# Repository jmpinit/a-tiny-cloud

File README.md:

# A Tiny Cloud

**The Goal**: serve a blog from a load-balanced cloud of networked ATtiny10 microcontrollers.

**The Plan:**

1. Make a device that can program and communicate with an array of ATtiny10s via USB
2. Use the TUN/TAP driver in Linux to create a network interface for each ATtiny10. Behind the scenes data is shuffled over USB and then over serial to and from the microcontrollers.
3. Set up NGINX to load-balance requests from the WWW across the microcontrollers.
4. Write a blog engine in AVR assembly.
5. Uh...
6. Profit?

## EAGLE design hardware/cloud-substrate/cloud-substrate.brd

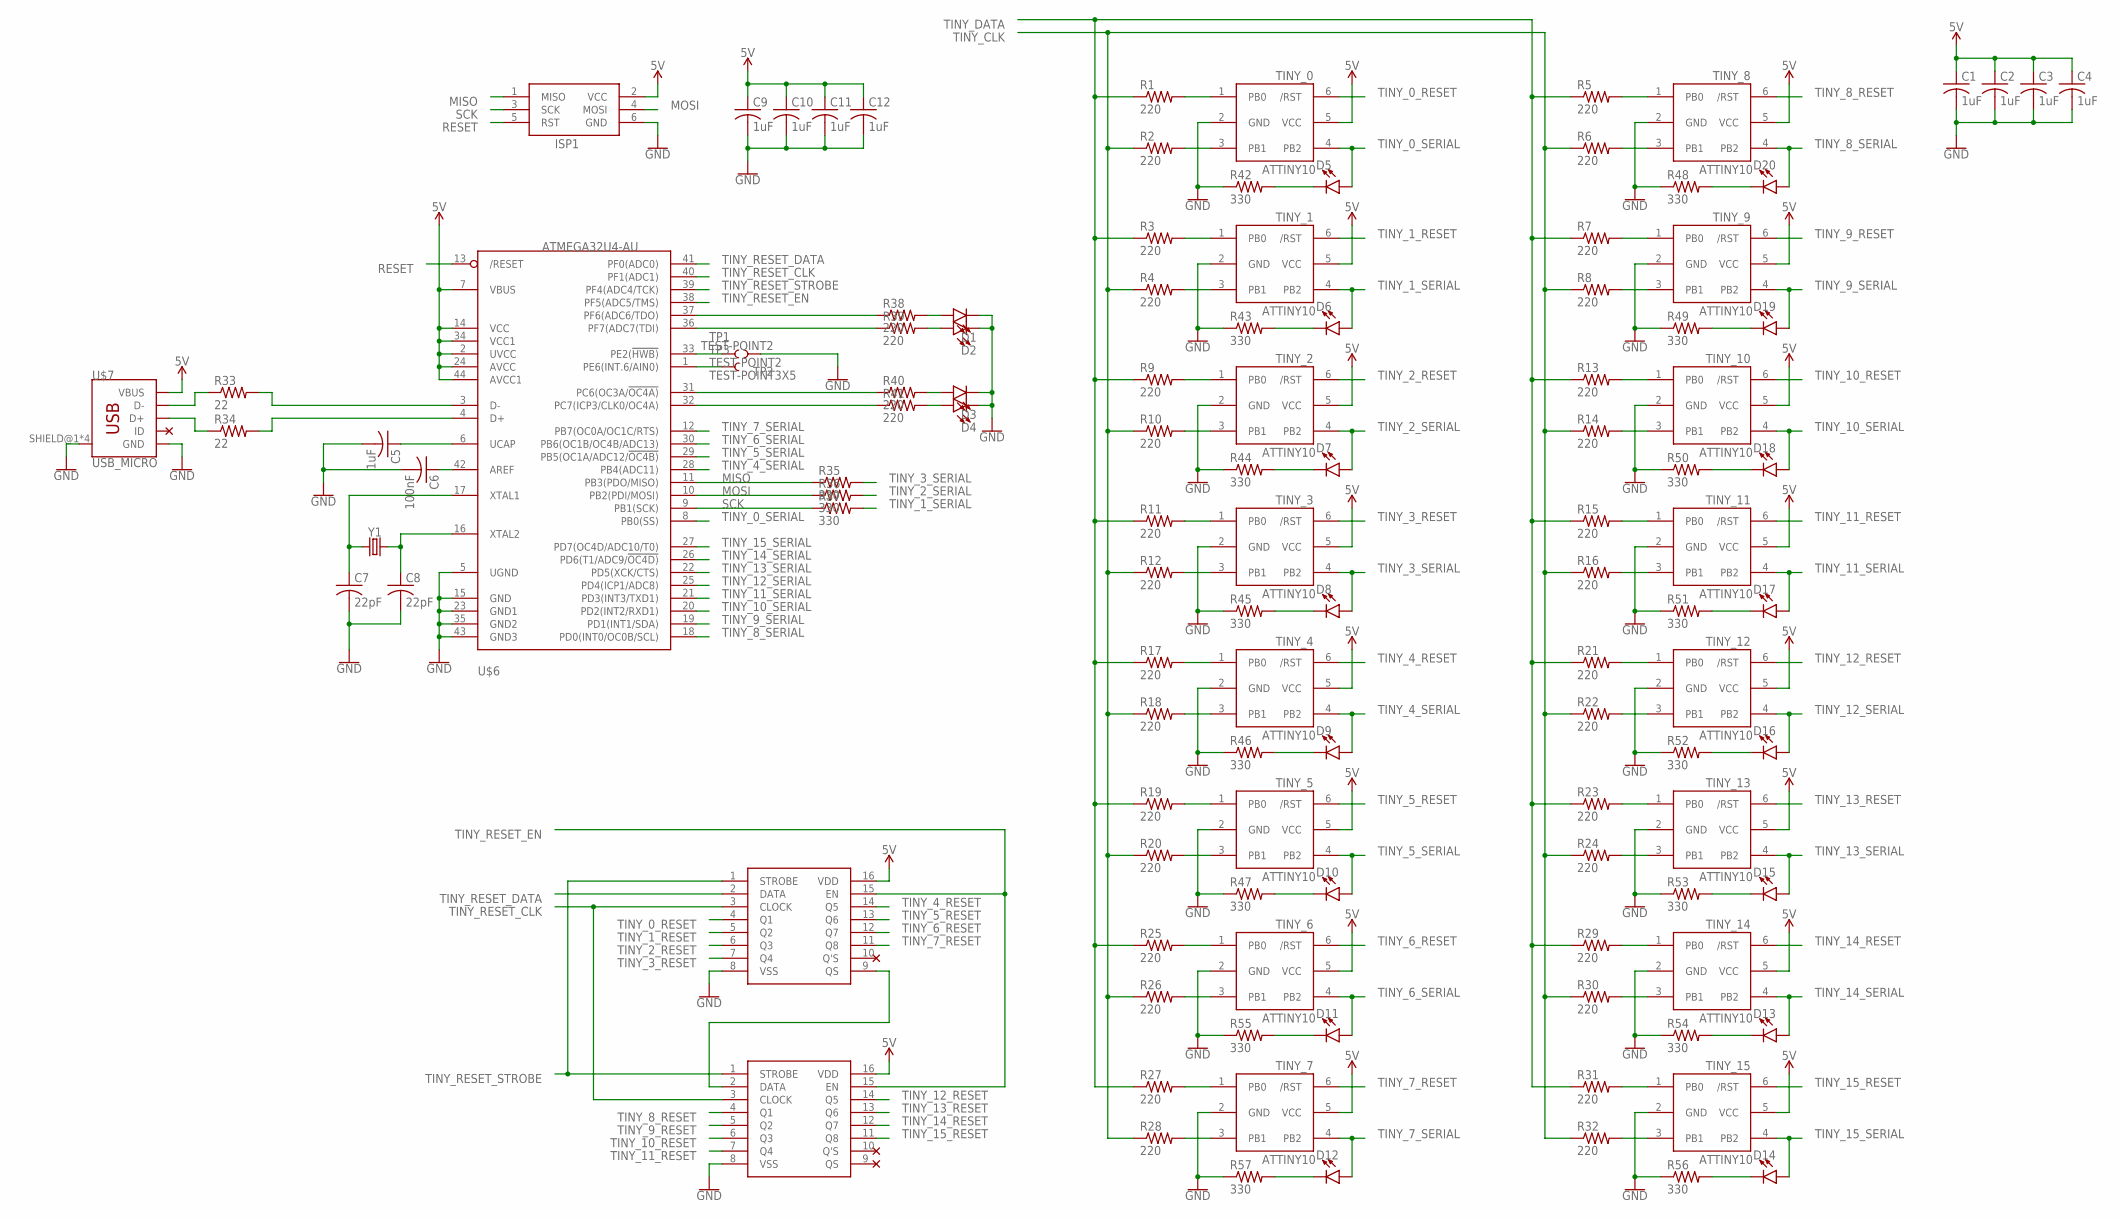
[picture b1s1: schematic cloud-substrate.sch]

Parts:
C1, C2, C3, C4, C9, C10, C11, C12: 1uF; C0805
C5: 1uF; C0402
C6: 100nF; C0402
C7, C8: 22pF; C0402
D1, D2, D3, D4, D5, D6, D7, D8, D9, D10, D11, D12, D13, D14, D15, D16, D17, D18, D19, D20: LED0603; LED-0603
ISP1: AVRISP-6; AVRISP
R1, R2, R3, R4, R5, R6, R7, R8, R9, R10, R11, R12, R13, R14, R15, R16, R17, R18, R19, R20, R21, R22, R23, R24, R25, R26, R27, R28, R29, R30, R31, R32, R38, R39, R40, R41: 220; R0402
R33, R34: 22; R0402
R35, R36, R37, R42, R43, R44, R45, R46, R47, R48, R49, R50, R51, R52, R53, R54, R55, R56, R57: 330; R0402
TINY_0, TINY_1, TINY_2, TINY_3, TINY_4, TINY_5, TINY_6, TINY_7, TINY_8, TINY_9, TINY_10, TINY_11, TINY_12, TINY_13, TINY_14, TINY_15: ATTINY10; SOT23-6
TP1, TP2: TEST-POINT2; PAD.02X.02
TP3: TEST-POINT3X5; PAD.03X.05
U$1, U$2: CD4094B; TSSOP16
U$6: ATMEGA32U4-AU; TQFP44
U$7: USB_MICRO; USB_FCI_10118194
Y1: CRYSTALSMD-3.2X2.5; CRYSTAL-SMD-3.2X2.5MM

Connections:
5V: C1.1, C2.1, C3.1, C4.1, C9.1, C10.1, C11.1, C12.1, ISP1.2 (VCC), TINY_0.5 (VCC), TINY_1.5 (VCC), TINY_2.5 (VCC), TINY_3.5 (VCC), TINY_4.5 (VCC), TINY_5.5 (VCC), TINY_6.5 (VCC), TINY_7.5 (VCC), TINY_8.5 (VCC), TINY_9.5 (VCC), TINY_10.5 (VCC), TINY_11.5 (VCC), TINY_12.5 (VCC), TINY_13.5 (VCC), TINY_14.5 (VCC), TINY_15.5 (VCC), U$1.16 (VDD), U$2.16 (VDD), U$6.2 (UVCC), U$6.7 (VBUS), U$6.14 (VCC), U$6.24 (AVCC), U$6.34 (VCC1), U$6.44 (AVCC1), U$7.1 (VBUS)
GND: C1.2, C2.2, C3.2, C4.2, C5.2, C6.2, C7.2, C8.2, C9.2, C10.2, C11.2, C12.2, D1.C, D2.C, D3.C, D4.C, ISP1.6 (GND), R42.1, R43.1, R44.1, R45.1, R46.1, R47.1, R48.1, R49.1, R50.1, R51.1, R52.1, R53.1, R54.1, R55.1, R56.1, R57.1, TINY_0.2 (GND), TINY_1.2 (GND), TINY_2.2 (GND), TINY_3.2 (GND), TINY_4.2 (GND), TINY_5.2 (GND), TINY_6.2 (GND), TINY_7.2 (GND), TINY_8.2 (GND), TINY_9.2 (GND), TINY_10.2 (GND), TINY_11.2 (GND), TINY_12.2 (GND), TINY_13.2 (GND), TINY_14.2 (GND), TINY_15.2 (GND), TP2.P$1, U$1.8 (VSS), U$2.8 (VSS), U$6.5 (UGND), U$6.15 (GND), U$6.23 (GND1), U$6.35 (GND2), U$6.43 (GND3), U$7.5 (GND), U$7.SHIELD@1 (SHIELD), U$7.SHIELD@2 (SHIELD), U$7.SHIELD@3 (SHIELD), U$7.SHIELD@4 (SHIELD)
MISO: ISP1.1 (MISO), R35.1, U$6.11 (PB3(PDO/MISO))
MOSI: ISP1.4 (MOSI), R36.1, U$6.10 (PB2(PDI/MOSI))
unnamed: R3.2, TINY_1.1 (PB0)
unnamed: R4.2, TINY_1.3 (PB1)
unnamed: R1.2, TINY_0.1 (PB0)
unnamed: R2.2, TINY_0.3 (PB1)
unnamed: R33.1, U$7.2 (D-)
unnamed: R34.1, U$7.3 (D+)
unnamed: R33.2, U$6.3 (D-)
unnamed: R34.2, U$6.4 (D+)
unnamed: U$1.9 (QS), U$2.2 (DATA)
unnamed: R5.2, TINY_8.1 (PB0)
unnamed: R6.2, TINY_8.3 (PB1)
unnamed: C5.1, U$6.6 (UCAP)
unnamed: C6.1, U$6.42 (AREF)
unnamed: R7.2, TINY_9.1 (PB0)
unnamed: R8.2, TINY_9.3 (PB1)
unnamed: C7.1, U$6.17 (XTAL1), Y1.1
unnamed: C8.1, U$6.16 (XTAL2), Y1.3 (2)
unnamed: R9.2, TINY_2.1 (PB0)
unnamed: R10.2, TINY_2.3 (PB1)
unnamed: TP1.P$1, U$6.33 (PE2(!HWB))
unnamed: R38.1, U$6.37 (PF6(ADC6/TDO))
unnamed: R11.2, TINY_3.1 (PB0)
unnamed: R12.2, TINY_3.3 (PB1)
unnamed: R39.1, U$6.36 (PF7(ADC7(TDI))
unnamed: R40.1, U$6.31 (PC6(OC3A/!OC4A))
unnamed: R13.2, TINY_10.1 (PB0)
unnamed: R14.2, TINY_10.3 (PB1)
unnamed: R41.1, U$6.32 (PC7(ICP3/CLK0/OC4A))
unnamed: D1.A, R38.2
unnamed: R15.2, TINY_11.1 (PB0)
unnamed: R16.2, TINY_11.3 (PB1)
unnamed: D2.A, R39.2
unnamed: D3.A, R40.2
unnamed: R17.2, TINY_4.1 (PB0)
unnamed: R18.2, TINY_4.3 (PB1)
unnamed: D4.A, R41.2
unnamed: D7.C, R44.2
unnamed: R19.2, TINY_5.1 (PB0)
unnamed: R20.2, TINY_5.3 (PB1)
unnamed: TP3.P$1, U$6.1 (PE6(INT.6/AIN0))
unnamed: D8.C, R45.2
unnamed: R21.2, TINY_12.1 (PB0)
unnamed: R22.2, TINY_12.3 (PB1)
unnamed: D9.C, R46.2
unnamed: D10.C, R47.2
unnamed: R23.2, TINY_13.1 (PB0)
unnamed: R24.2, TINY_13.3 (PB1)
unnamed: D11.C, R55.2
unnamed: D12.C, R57.2
unnamed: R25.2, TINY_6.1 (PB0)
unnamed: R26.2, TINY_6.3 (PB1)
unnamed: D14.C, R56.2
unnamed: D13.C, R54.2
unnamed: R27.2, TINY_7.1 (PB0)
unnamed: R28.2, TINY_7.3 (PB1)
unnamed: D15.C, R53.2
unnamed: D16.C, R52.2
unnamed: R29.2, TINY_14.1 (PB0)
unnamed: R30.2, TINY_14.3 (PB1)
unnamed: D17.C, R51.2
unnamed: D18.C, R50.2
unnamed: R31.2, TINY_15.1 (PB0)
unnamed: R32.2, TINY_15.3 (PB1)
unnamed: D20.C, R48.2
unnamed: D19.C, R49.2
unnamed: D5.C, R42.2
unnamed: D6.C, R43.2
RESET: ISP1.5 (RST), U$6.13 (/RESET)
SCK: ISP1.3 (SCK), R37.1, U$6.9 (PB1(SCK))
TINY_0_RESET: TINY_0.6 (/RST), U$1.4 (Q1)
TINY_0_SERIAL: D5.A, TINY_0.4 (PB2), U$6.8 (PB0(SS))
TINY_1_RESET: TINY_1.6 (/RST), U$1.5 (Q2)
TINY_1_SERIAL: D6.A, R37.2, TINY_1.4 (PB2)
TINY_2_RESET: TINY_2.6 (/RST), U$1.6 (Q3)
TINY_2_SERIAL: D7.A, R36.2, TINY_2.4 (PB2)
TINY_3_RESET: TINY_3.6 (/RST), U$1.7 (Q4)
TINY_3_SERIAL: D8.A, R35.2, TINY_3.4 (PB2)
TINY_4_RESET: TINY_4.6 (/RST), U$1.14 (Q5)
TINY_4_SERIAL: D9.A, TINY_4.4 (PB2), U$6.28 (PB4(ADC11))
TINY_5_RESET: TINY_5.6 (/RST), U$1.13 (Q6)
TINY_5_SERIAL: D10.A, TINY_5.4 (PB2), U$6.29 (PB5(OC1A/ADC12/!OC4B))
TINY_6_RESET: TINY_6.6 (/RST), U$1.12 (Q7)
TINY_6_SERIAL: D11.A, TINY_6.4 (PB2), U$6.30 (PB6(OC1B/OC4B/ADC13))
TINY_7_RESET: TINY_7.6 (/RST), U$1.11 (Q8)
TINY_7_SERIAL: D12.A, TINY_7.4 (PB2), U$6.12 (PB7(OC0A/OC1C/RTS))
TINY_8_RESET: TINY_8.6 (/RST), U$2.4 (Q1)
TINY_8_SERIAL: D20.A, TINY_8.4 (PB2), U$6.18 (PD0(INT0/OC0B/SCL))
TINY_9_RESET: TINY_9.6 (/RST), U$2.5 (Q2)
TINY_9_SERIAL: D19.A, TINY_9.4 (PB2), U$6.19 (PD1(INT1/SDA))
TINY_10_RESET: TINY_10.6 (/RST), U$2.6 (Q3)
TINY_10_SERIAL: D18.A, TINY_10.4 (PB2), U$6.20 (PD2(INT2/RXD1))
TINY_11_RESET: TINY_11.6 (/RST), U$2.7 (Q4)
TINY_11_SERIAL: D17.A, TINY_11.4 (PB2), U$6.21 (PD3(INT3/TXD1))
TINY_12_RESET: TINY_12.6 (/RST), U$2.14 (Q5)
TINY_12_SERIAL: D16.A, TINY_12.4 (PB2), U$6.25 (PD4(ICP1/ADC8))
TINY_13_RESET: TINY_13.6 (/RST), U$2.13 (Q6)
TINY_13_SERIAL: D15.A, TINY_13.4 (PB2), U$6.22 (PD5(XCK/CTS))
TINY_14_RESET: TINY_14.6 (/RST), U$2.12 (Q7)
TINY_14_SERIAL: D13.A, TINY_14.4 (PB2), U$6.26 (PD6(T1/ADC9/!OC4D))
TINY_15_RESET: TINY_15.6 (/RST), U$2.11 (Q8)
TINY_15_SERIAL: D14.A, TINY_15.4 (PB2), U$6.27 (PD7(OC4D/ADC10/T0))
TINY_CLK: R2.1, R4.1, R6.1, R8.1, R10.1, R12.1, R14.1, R16.1, R18.1, R20.1, R22.1, R24.1, R26.1, R28.1, R30.1, R32.1
TINY_DATA: R1.1, R3.1, R5.1, R7.1, R9.1, R11.1, R13.1, R15.1, R17.1, R19.1, R21.1, R23.1, R25.1, R27.1, R29.1, R31.1
TINY_RESET_CLK: U$1.3 (CLOCK), U$2.3 (CLOCK), U$6.40 (PF1(ADC1))
TINY_RESET_DATA: U$1.2 (DATA), U$6.41 (PF0(ADC0))
TINY_RESET_EN: U$1.15 (EN), U$2.15 (EN), U$6.38 (PF5(ADC5/TMS))
TINY_RESET_STROBE: U$1.1 (STROBE), U$2.1 (STROBE), U$6.39 (PF4(ADC4/TCK))

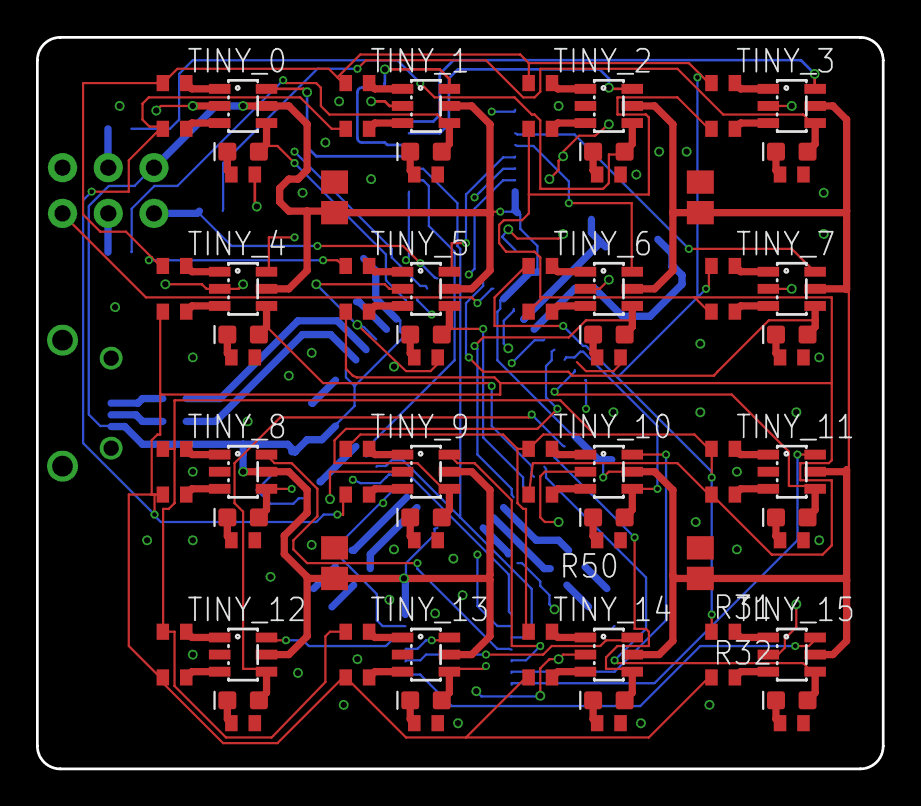
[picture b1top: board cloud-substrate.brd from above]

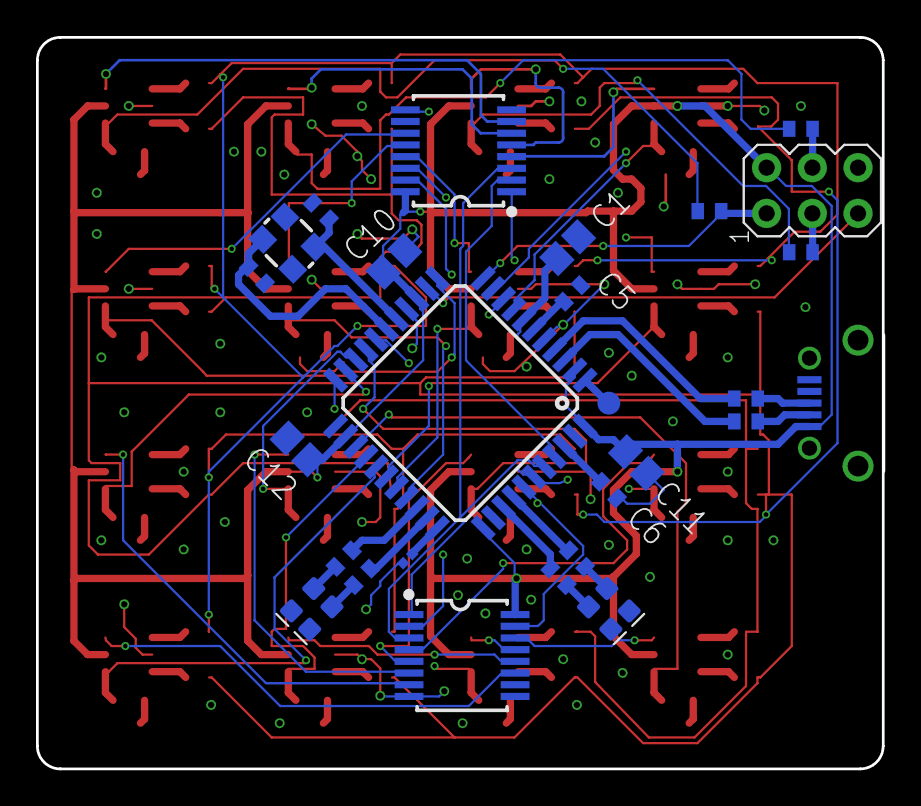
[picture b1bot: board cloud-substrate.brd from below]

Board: 4 copper layers, 47.0 x 40.6 mm, 114 parts (30 on the bottom side), 111 nets.

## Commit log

2017-09-03 Schematic and explanation
2017-09-03 Make pretty and HWB pin jumper point
2017-09-03 v0 PCB design

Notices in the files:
parts and their libraries:
SparkFun-LED: Licensing: Creative Commons ShareAlike 4.0 International - https://creativecommons.org/licenses/by-sa/4.0
